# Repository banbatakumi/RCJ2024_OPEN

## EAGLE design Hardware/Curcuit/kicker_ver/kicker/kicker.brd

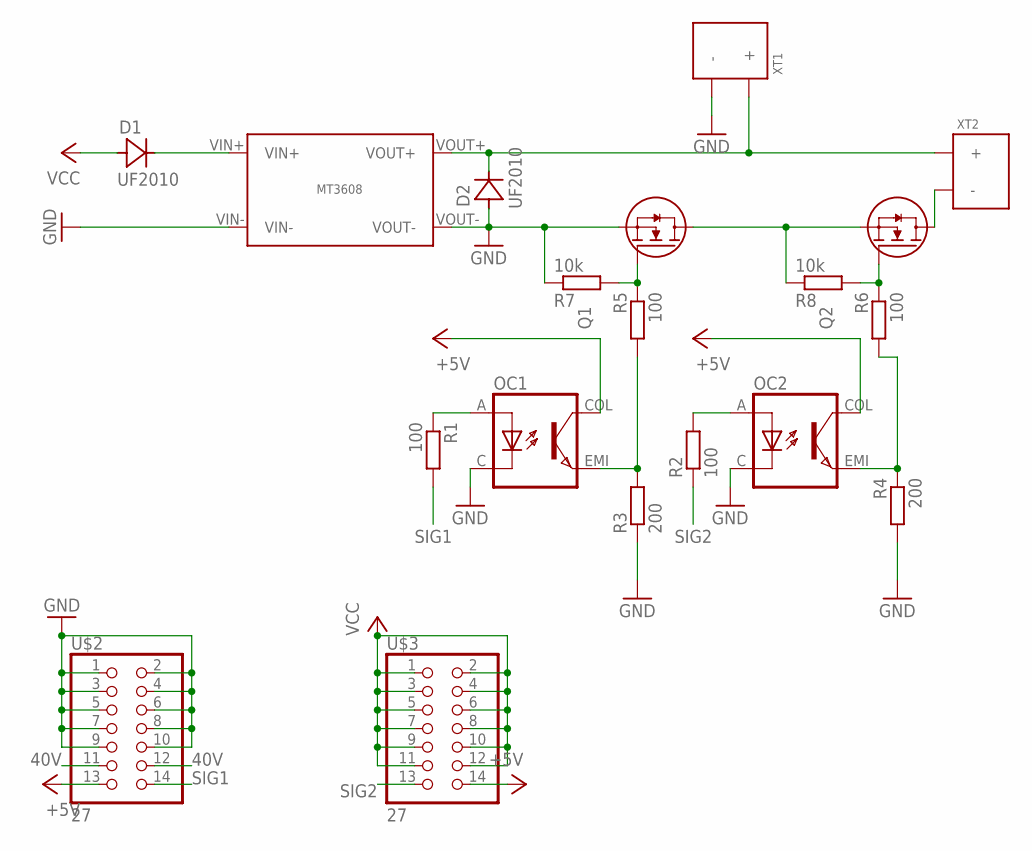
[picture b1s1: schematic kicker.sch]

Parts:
D1, D2: UF2010
OC1, OC2: TL293(GB); SOIC127P700X230-4N
Q1, Q2: NP52N06SLG; TO230P1040X230-3N
R1, R2, R5, R6: 100; R0603
R3, R4: 200; R0603
R7, R8: 10k; R0603
U$1: MT3608
U$2, U$3: 27; 2*7
XT1, XT2: XT30PW-F

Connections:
40V: D2.C, U$1.VOUT+, U$2.11, U$2.12, XT1.+, XT2.+
+5V: OC1.COL, OC2.COL, U$2.13, U$3.14
GND: D2.A, OC1.C, OC2.C, Q1.S, R3.1, R4.2, R7.1, U$1.VIN-, U$1.VOUT-, U$2.1, U$2.2, U$2.3, U$2.4, U$2.5, U$2.6, U$2.7, U$2.8, U$2.9, U$2.10, XT1.-
unnamed: D1.C, U$1.VIN+
unnamed: Q1.D, Q2.S, R8.1
unnamed: OC1.EMI, R3.2, R5.2
unnamed: Q2.D, XT2.-
unnamed: OC1.A, R1.1
unnamed: OC2.A, R2.2
unnamed: OC2.EMI, R4.1, R6.2
unnamed: Q1.G, R5.1, R7.2
unnamed: Q2.G, R6.1, R8.2
SIG1: R1.2, U$2.14
SIG2: R2.1, U$3.13
VCC: D1.A, U$3.1, U$3.2, U$3.3, U$3.4, U$3.5, U$3.6, U$3.7, U$3.8, U$3.9, U$3.10, U$3.11, U$3.12

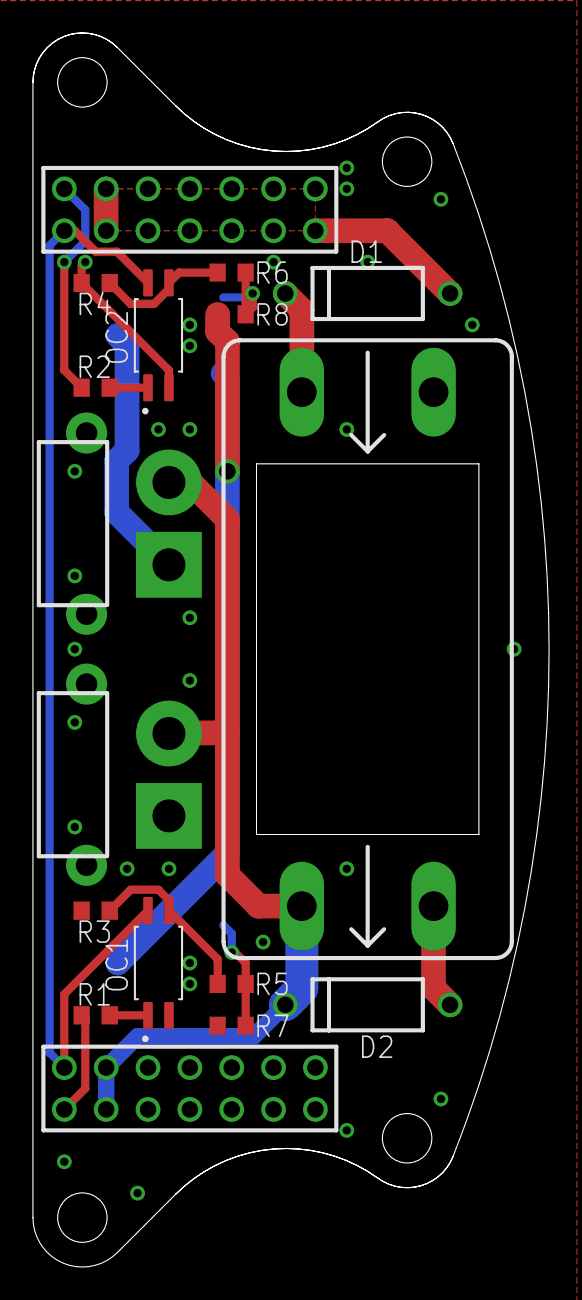
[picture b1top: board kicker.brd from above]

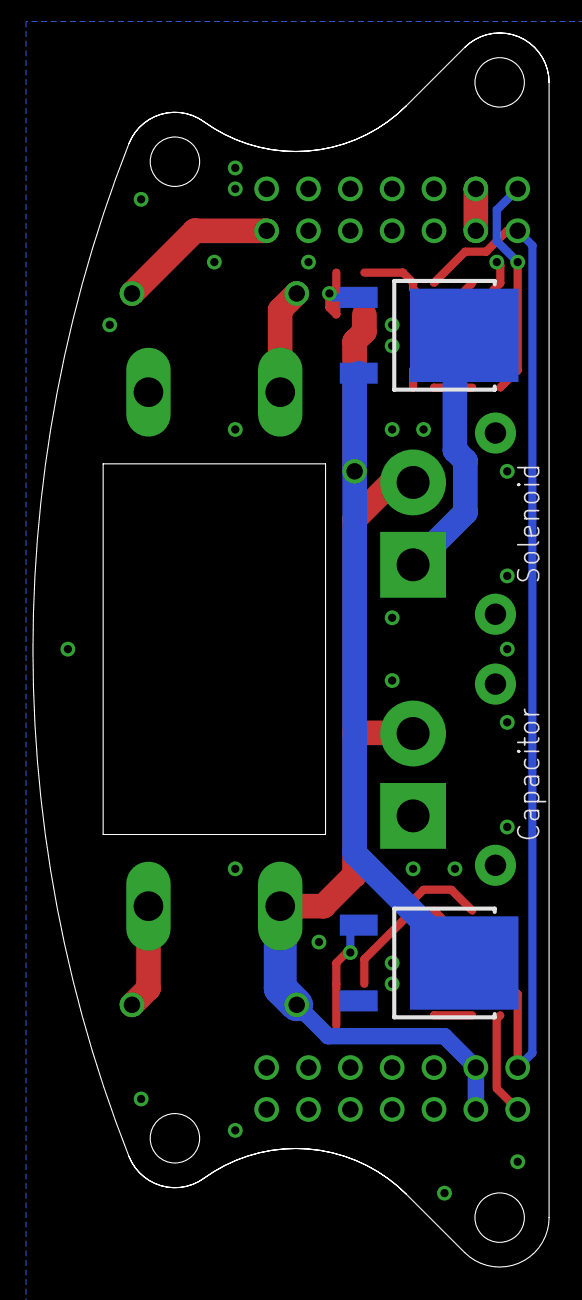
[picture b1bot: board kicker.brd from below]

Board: 2 copper layers, 31.3 x 74.9 mm, 19 parts (2 on the bottom side), 15 nets.

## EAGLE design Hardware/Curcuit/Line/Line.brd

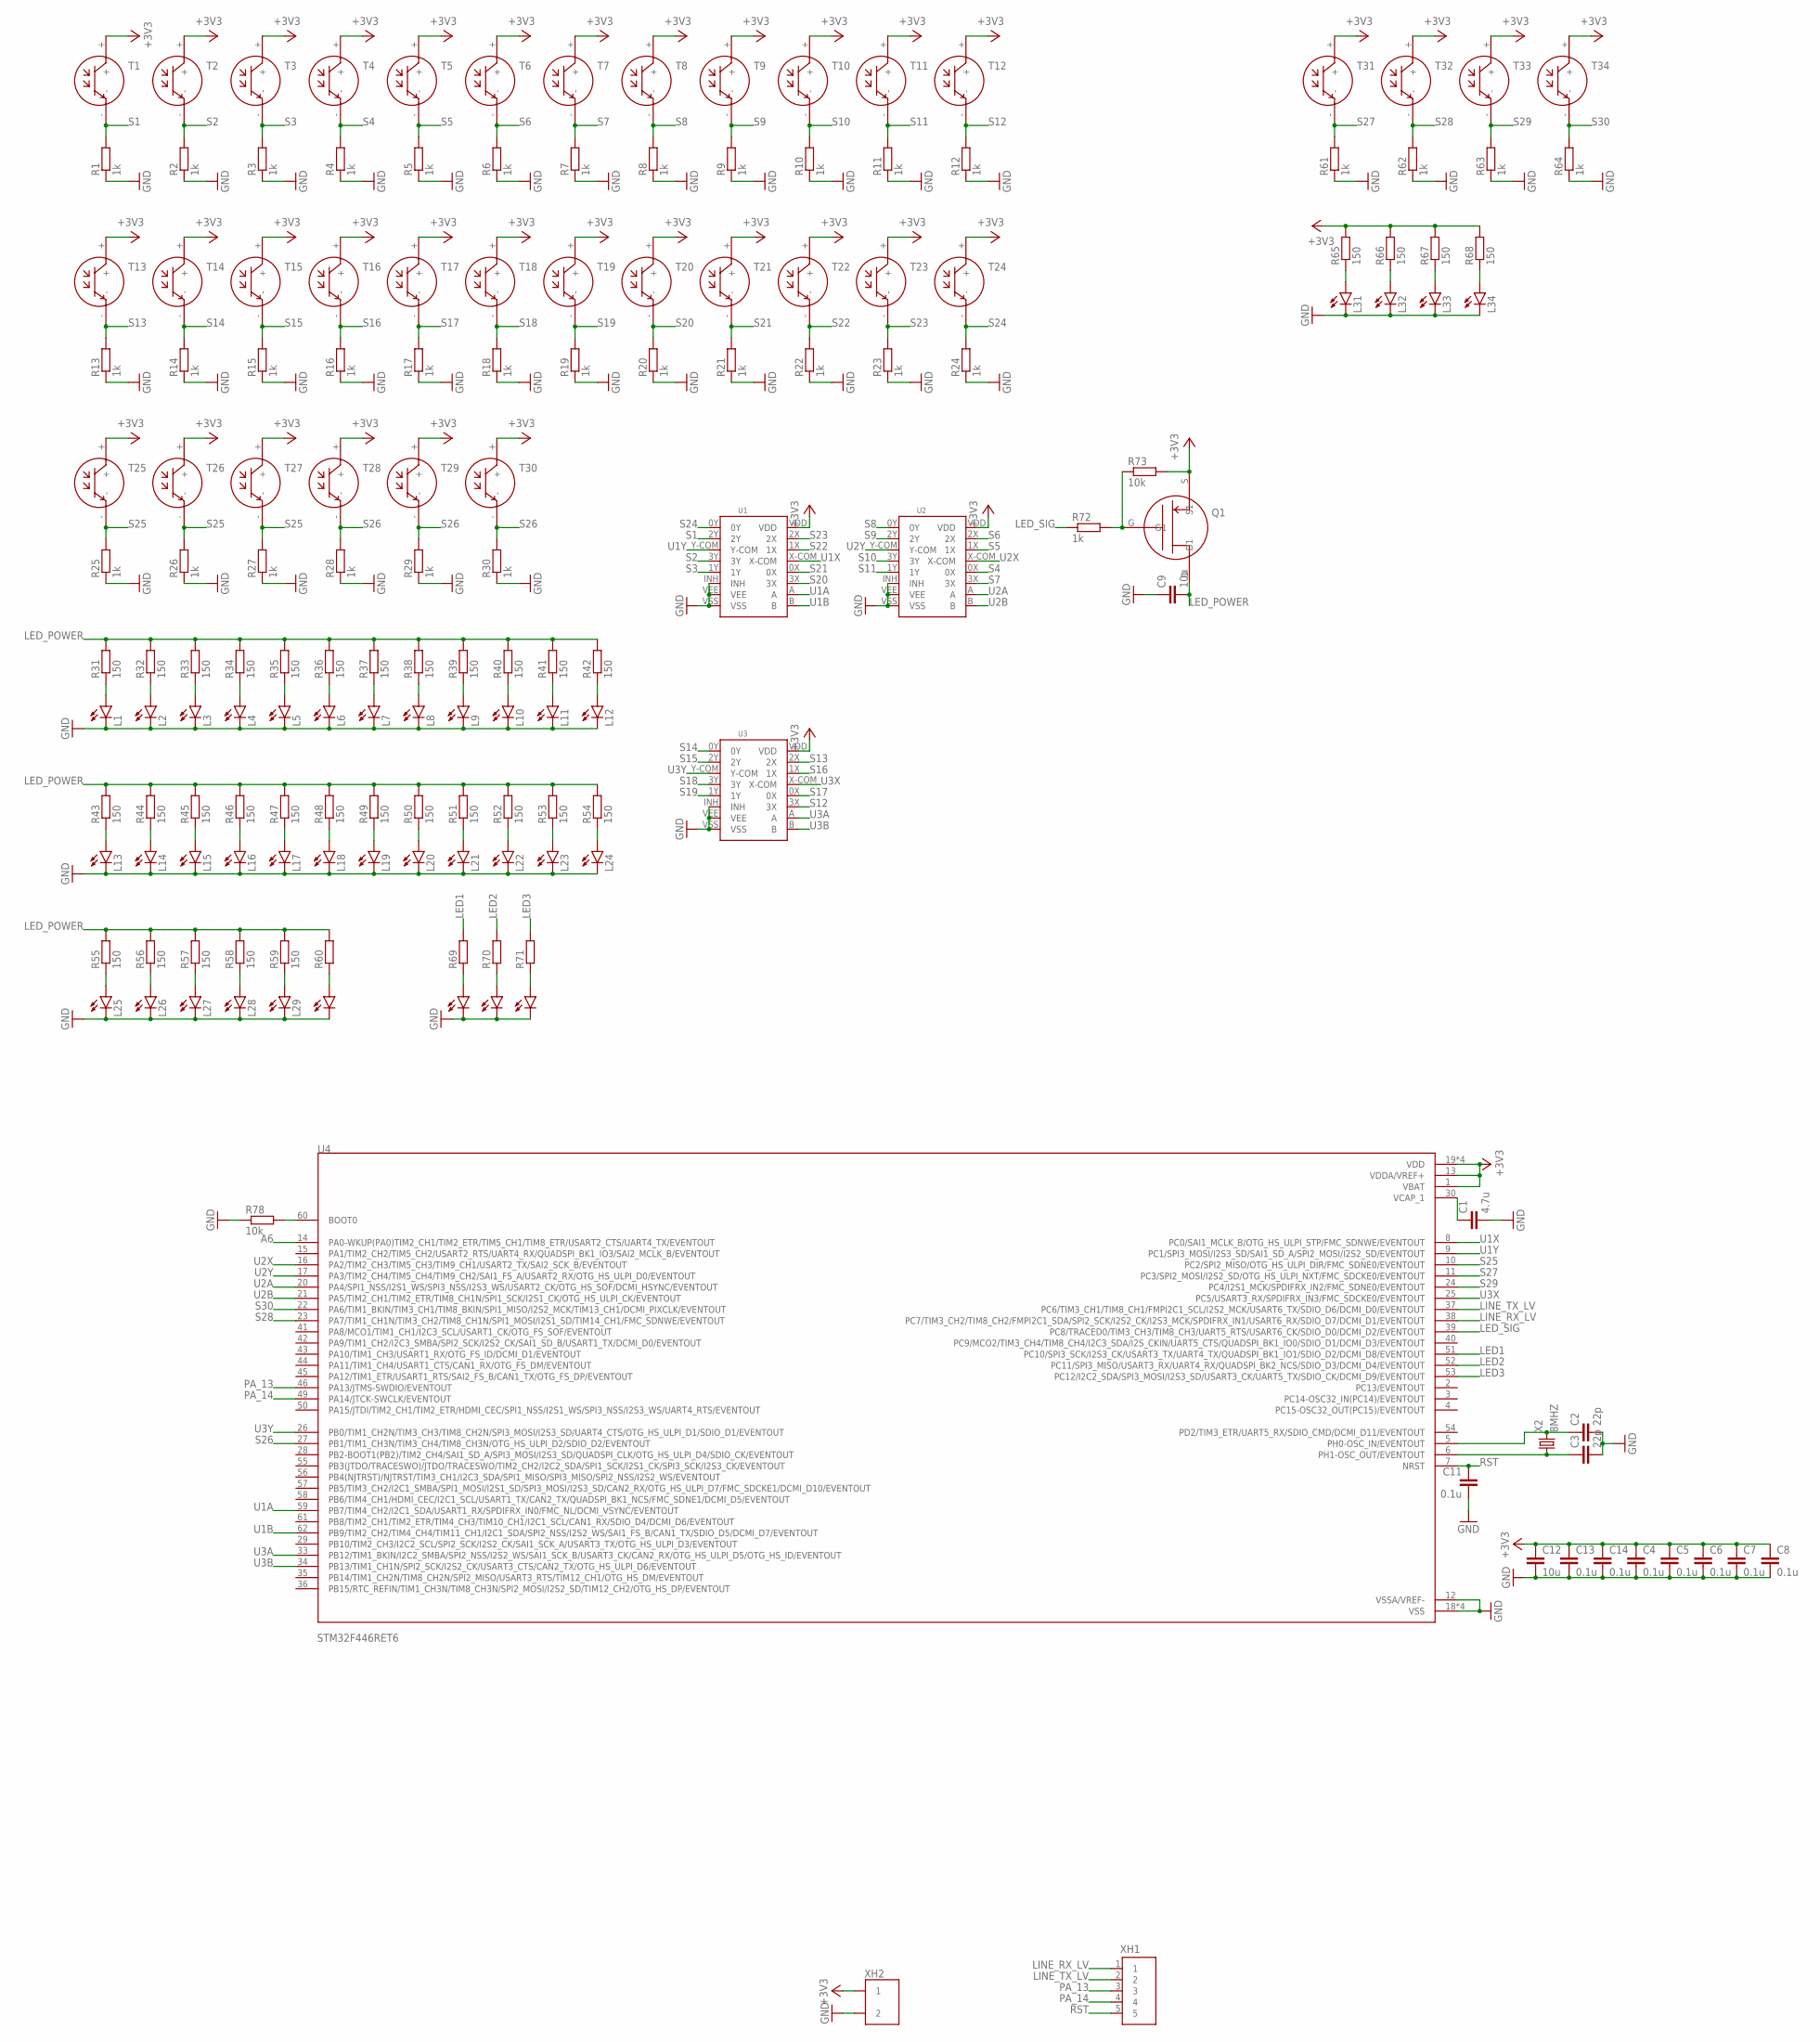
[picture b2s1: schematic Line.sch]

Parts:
C1: 4.7u; C0603
C2, C3: 22p; C0603
C4, C5, C6, C7, C8, C11, C13, C14: 0.1u; C0603
C9, C12: 10u; C0805
L1, L2, L3, L4, L5, L6, L7, L8, L9, L10, L11, L12, L13, L14, L15, L16, L17, L18, L19, L20, L21, L22, L23, L24, L25, L26, L27, L28, L29, L30, L31, L32, L33, L34, L35, L36, L37: SML-E12P8WT86; LED_SML-LXFM0603SIC-TR
Q1: TJ60S04M3L; DPACK
R1, R2, R3, R4, R5, R6, R7, R8, R9, R10, R11, R12, R13, R14, R15, R16, R17, R18, R19, R20, R21, R22, R23, R24, R25, R26, R27, R28, R29, R30, R61, R62, R63, R64, R72: 1k; R0603
R31, R32, R33, R34, R35, R36, R37, R38, R39, R40, R41, R42, R43, R44, R45, R46, R47, R48, R49, R50, R51, R52, R53, R54, R55, R56, R57, R58, R59, R60, R65, R66, R67, R68, R69, R70, R71: 150; R0603
R73, R78: 10k; R0603
T1, T2, T3, T4, T5, T6, T7, T8, T9, T10, T11, T12, T13, T14, T15, T16, T17, T18, T19, T20, T21, T22, T23, T24, T25, T26, T27, T28, T29, T30, T31, T32, T33, T34: NJL7302L-F3
U1, U2, U3: TC4051BP
U4: STM32F446RET6; QFP50P1200X1200X160-64N
X2: 8MHZ; 16MHZ
XH1: 5B
XH2: 2B

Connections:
+3V3: C4.1, C5.1, C6.1, C7.1, C8.1, C12.1, C13.1, C14.1, Q1.S (S1), R65.2, R66.2, R67.2, R68.2, R73.2, T1.+, T2.+, T3.+, T4.+, T5.+, T6.+, T7.+, T8.+, T9.+, T10.+, T11.+, T12.+, T13.+, T14.+, T15.+, T16.+, T17.+, T18.+, T19.+, T20.+, T21.+, T22.+, T23.+, T24.+, T25.+, T26.+, T27.+, T28.+, T29.+, T30.+, T31.+, T32.+, T33.+, T34.+, U1.VDD, U2.VDD, U3.VDD, U4.1 (VBAT), U4.13 (VDDA/VREF+), U4.19 (VDD), U4.32 (VDD), U4.48 (VDD), U4.64 (VDD), XH2.P$1 (1)
A6: U4.14 (PA0-WKUP(PA0)TIM2_CH1/TIM2_ETR/TIM5_CH1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)
GND: C1.2, C2.2, C3.2, C4.2, C5.2, C6.2, C7.2, C8.2, C9.1, C11.2, C12.2, C13.2, C14.2, L1.C, L2.C, L3.C, L4.C, L5.C, L6.C, L7.C, L8.C, L9.C, L10.C, L11.C, L12.C, L13.C, L14.C, L15.C, L16.C, L17.C, L18.C, L19.C, L20.C, L21.C, L22.C, L23.C, L24.C, L25.C, L26.C, L27.C, L28.C, L29.C, L30.C, L31.C, L32.C, L33.C, L34.C, L35.C, L36.C, L37.C, R1.1, R2.1, R3.1, R4.1, R5.1, R6.1, R7.1, R8.1, R9.1, R10.1, R11.1, R12.1, R13.1, R14.1, R15.1, R16.1, R17.1, R18.1, R19.1, R20.1, R21.1, R22.1, R23.1, R24.1, R25.1, R26.1, R27.1, R28.1, R29.1, R30.1, R61.1, R62.1, R63.1, R64.1, R78.1, U1.INH, U1.VEE, U1.VSS, U2.INH, U2.VEE, U2.VSS, U3.INH, U3.VEE, U3.VSS, U4.12 (VSSA/VREF-), U4.18 (VSS), U4.31 (VSS), U4.47 (VSS), U4.63 (VSS), XH2.P$2 (2)
LED1: R69.2, U4.51 (PC10/SPI3_SCK/I2S3_CK/USART3_TX/UART4_T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)
LED2: R70.2, U4.52 (PC11/SPI3_MISO/USART3_RX/UART4_RX/QUADS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)
LED3: R71.2, U4.53 (PC12/I2C2_SDA/SPI3_MOSI/I2S3_SD/USART3_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)
LED_POWER: C9.2, Q1.D (D1), R31.2, R32.2, R33.2, R34.2, R35.2, R36.2, R37.2, R38.2, R39.2, R40.2, R41.2, R42.2, R43.2, R44.2, R45.2, R46.2, R47.2, R48.2, R49.2, R50.2, R51.2, R52.2, R53.2, R54.2, R55.2, R56.2, R57.2, R58.2, R59.2, R60.2
LED_SIG: R72.1, U4.39 (PC8/TRACED0/TIM3_CH3/TIM8_CH3/UART5_RTS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)
LINE_RX_LV: U4.38 (PC7/TIM3_CH2/TIM8_CH2/FMPI2C1_SDA/SPI2_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), XH1.1
LINE_TX_LV: U4.37 (PC6/TIM3_CH1/TIM8_CH1/FMPI2C1_SCL/I2S2_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), XH1.2
unnamed: L1.A, R31.1
unnamed: L2.A, R32.1
unnamed: L3.A, R33.1
unnamed: L4.A, R34.1
unnamed: L5.A, R35.1
unnamed: L6.A, R36.1
unnamed: L7.A, R37.1
unnamed: L8.A, R38.1
unnamed: L9.A, R39.1
unnamed: L10.A, R40.1
unnamed: L11.A, R41.1
unnamed: L12.A, R42.1
unnamed: L13.A, R43.1
unnamed: L14.A, R44.1
unnamed: L15.A, R45.1
unnamed: L16.A, R46.1
unnamed: L17.A, R47.1
unnamed: L18.A, R48.1
unnamed: L19.A, R49.1
unnamed: L20.A, R50.1
unnamed: L21.A, R51.1
unnamed: L22.A, R52.1
unnamed: L23.A, R53.1
unnamed: L24.A, R54.1
unnamed: L25.A, R55.1
unnamed: L26.A, R56.1
unnamed: L27.A, R57.1
unnamed: L28.A, R58.1
unnamed: L29.A, R59.1
unnamed: L30.A, R60.1
unnamed: L31.A, R65.1
unnamed: L32.A, R66.1
unnamed: L33.A, R67.1
unnamed: L34.A, R68.1
unnamed: L35.A, R69.1
unnamed: L36.A, R70.1
unnamed: L37.A, R71.1
unnamed: Q1.G (G1), R72.2, R73.1
unnamed: C1.1, U4.30 (VCAP_1)
unnamed: R78.2, U4.60 (BOOT0)
unnamed: C2.1, U4.5 (PH0-OSC_IN/EVENTOUT), X2.P$2 (2)
unnamed: C3.1, U4.6 (PH1-OSC_OUT/EVENTOUT), X2.P$1 (1)
PA_13: U4.46 (PA13/JTMS-SWDIO/EVENTOUT), XH1.3
PA_14: U4.49 (PA14/JTCK-SWCLK/EVENTOUT), XH1.4
RST: C11.1, U4.7 (NRST), XH1.5
S1: R1.2, T1.-, U1.2Y
S2: R2.2, T2.-, U1.3Y
S3: R3.2, T3.-, U1.1Y
S4: R4.2, T4.-, U2.0X
S5: R5.2, T5.-, U2.1X
S6: R6.2, T6.-, U2.2X
S7: R7.2, T7.-, U2.3X
S8: R8.2, T8.-, U2.0Y
S9: R9.2, T9.-, U2.2Y
S10: R10.2, T10.-, U2.3Y
S11: R11.2, T11.-, U2.1Y
S12: R12.2, T12.-, U3.3X
S13: R13.2, T13.-, U3.2X
S14: R14.2, T14.-, U3.0Y
S15: R15.2, T15.-, U3.2Y
S16: R16.2, T16.-, U3.1X
S17: R17.2, T17.-, U3.0X
S18: R18.2, T18.-, U3.3Y
S19: R19.2, T19.-, U3.1Y
S20: R20.2, T20.-, U1.3X
S21: R21.2, T21.-, U1.0X
S22: R22.2, T22.-, U1.1X
S23: R23.2, T23.-, U1.2X
S24: R24.2, T24.-, U1.0Y
S25: R25.2, R26.2, R27.2, T25.-, T26.-, T27.-, U4.10 (PC2/SPI2_MISO/OTG_HS_ULPI_DIR/FMC_SDNE0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)
S26: R28.2, R29.2, R30.2, T28.-, T29.-, T30.-, U4.27 (PB1/TIM1_CH3N/TIM3_CH4/TIM8_CH3N/OTG_HS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)
S27: R61.2, T31.-, U4.11 (PC3/SPI2_MOSI/I2S2_SD/OTG_HS_ULPI_NXT/F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)
S28: R62.2, T32.-, U4.23 (PA7/TIM1_CH1N/TIM3_CH2/TIM8_CH1N/SPI1_M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)
S29: R63.2, T33.-, U4.24 (PC4/I2S1_MCK/SPDIFRX_IN2/FMC_SDNE0/EVEN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)
S30: R64.2, T34.-, U4.22 (PA6/TIM1_BKIN/TIM3_CH1/TIM8_BKIN/SPI1_M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)
U1A: U1.A, U4.59 (PB7/TIM4_CH2/I2C1_SDA/USART1_RX/SPDIFRX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)
U1B: U1.B, U4.62 (PB9/TIM2_CH2/TIM4_CH4/TIM11_CH1/I2C1_SD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)
U1X: U1.X-COM, U4.8 (PC0/SAI1_MCLK_B/OTG_HS_ULPI_STP/FMC_SDN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)
U1Y: U1.Y-COM, U4.9 (PC1/SPI3_MOSI/I2S3_SD/SAI1_SD_A/SPI2_MO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)
U2A: U2.A, U4.20 (PA4/SPI1_NSS/I2S1_WS/SPI3_NSS/I2S3_WS/U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)
U2B: U2.B, U4.21 (PA5/TIM2_CH1/TIM2_ETR/TIM8_CH1N/SPI1_SC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)
U2X: U2.X-COM, U4.16 (PA2/TIM2_CH3/TIM5_CH3/TIM9_CH1/USART2_T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)
U2Y: U2.Y-COM, U4.17 (PA3/TIM2_CH4/TIM5_CH4/TIM9_CH2/SAI1_FS_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)
U3A: U3.A, U4.33 (PB12/TIM1_BKIN/I2C2_SMBA/SPI2_NSS/I2S2_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)
U3B: U3.B, U4.34 (PB13/TIM1_CH1N/SPI2_SCK/I2S2_CK/USART3_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)
U3X: U3.X-COM, U4.25 (PC5/USART3_RX/SPDIFRX_IN3/FMC_SDCKE0/EV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)
U3Y: U3.Y-COM, U4.26 (PB0/TIM1_CH2N/TIM3_CH3/TIM8_CH2N/SPI3_M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)

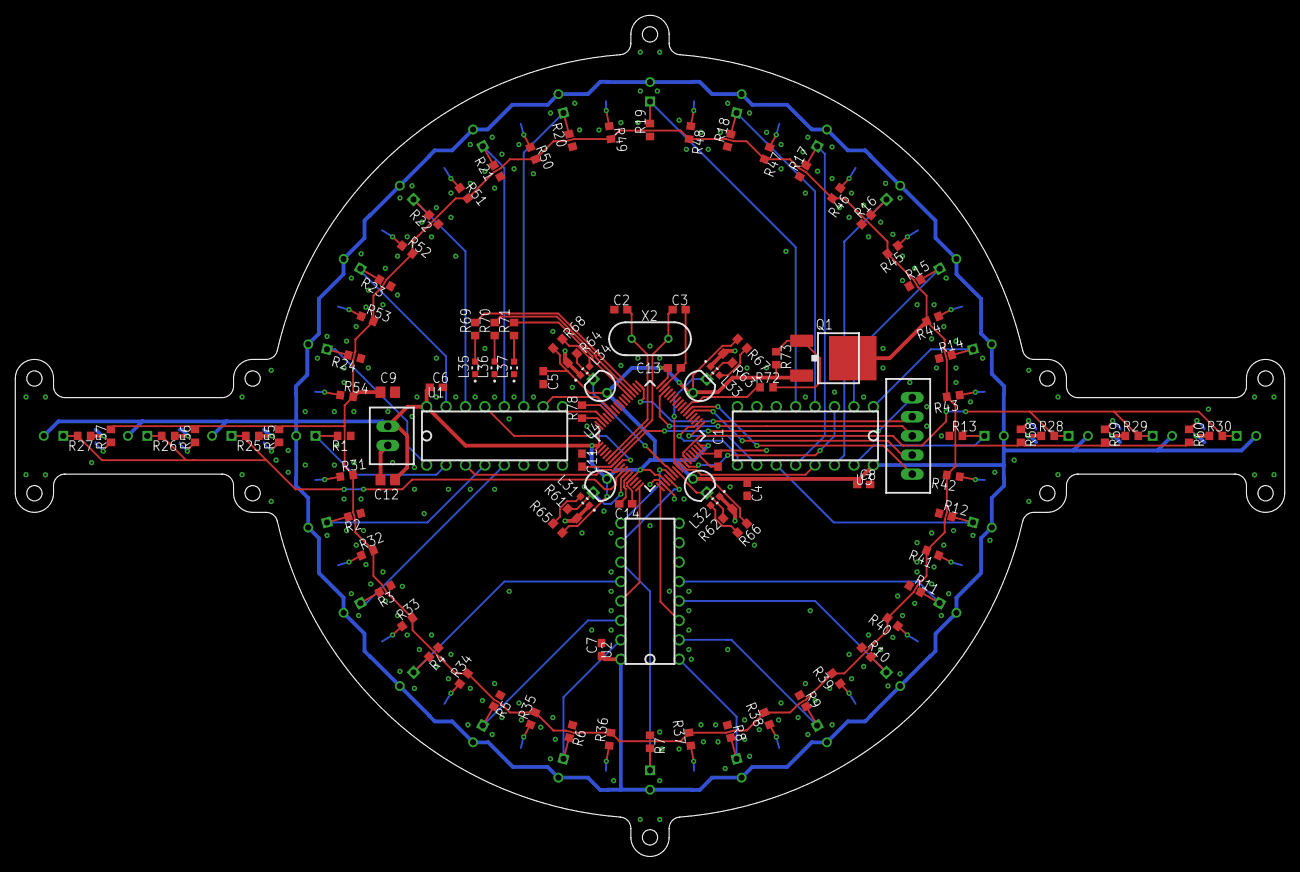
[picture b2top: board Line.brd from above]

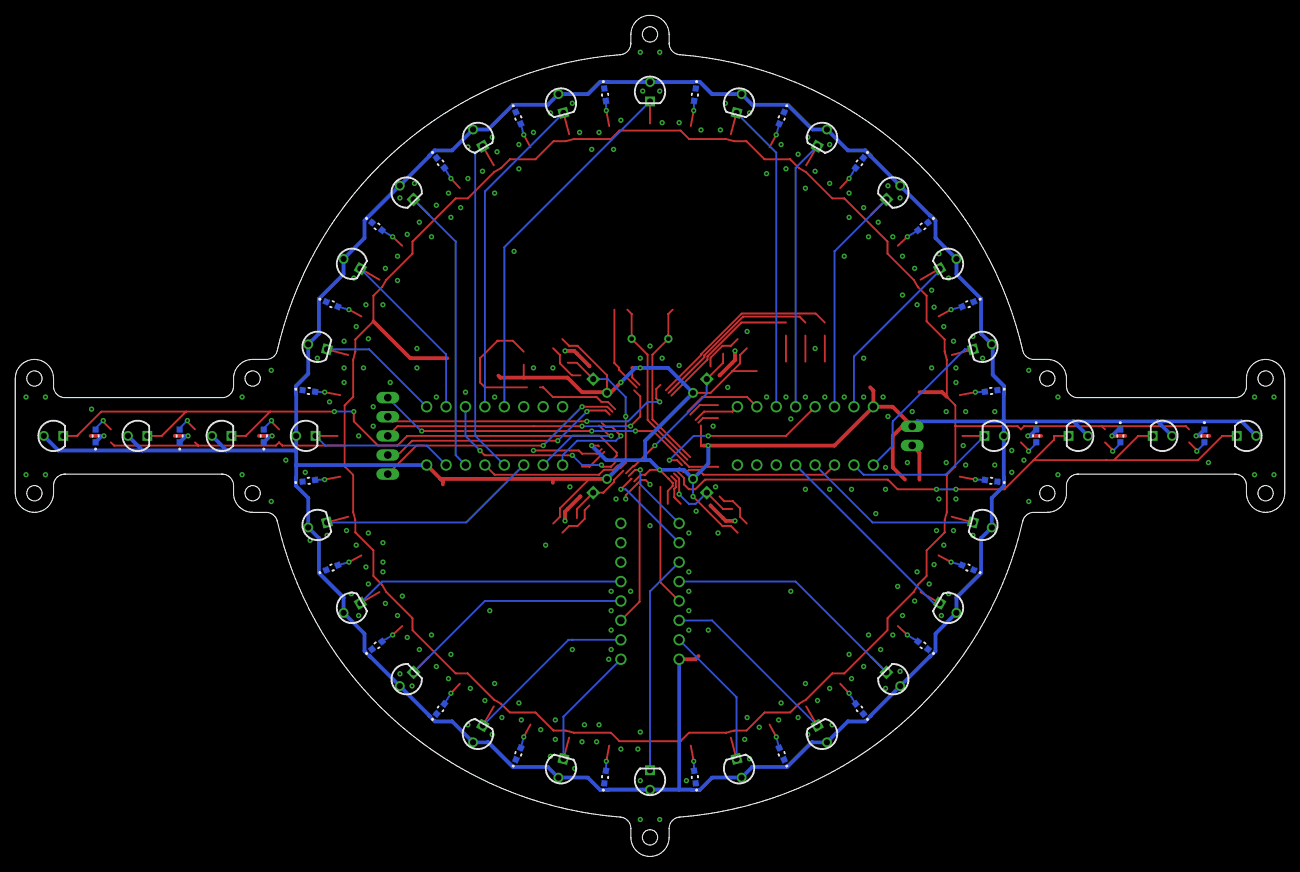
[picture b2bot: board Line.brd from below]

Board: 2 copper layers, 166.0 x 110.0 mm, 166 parts (60 on the bottom side), 96 nets.

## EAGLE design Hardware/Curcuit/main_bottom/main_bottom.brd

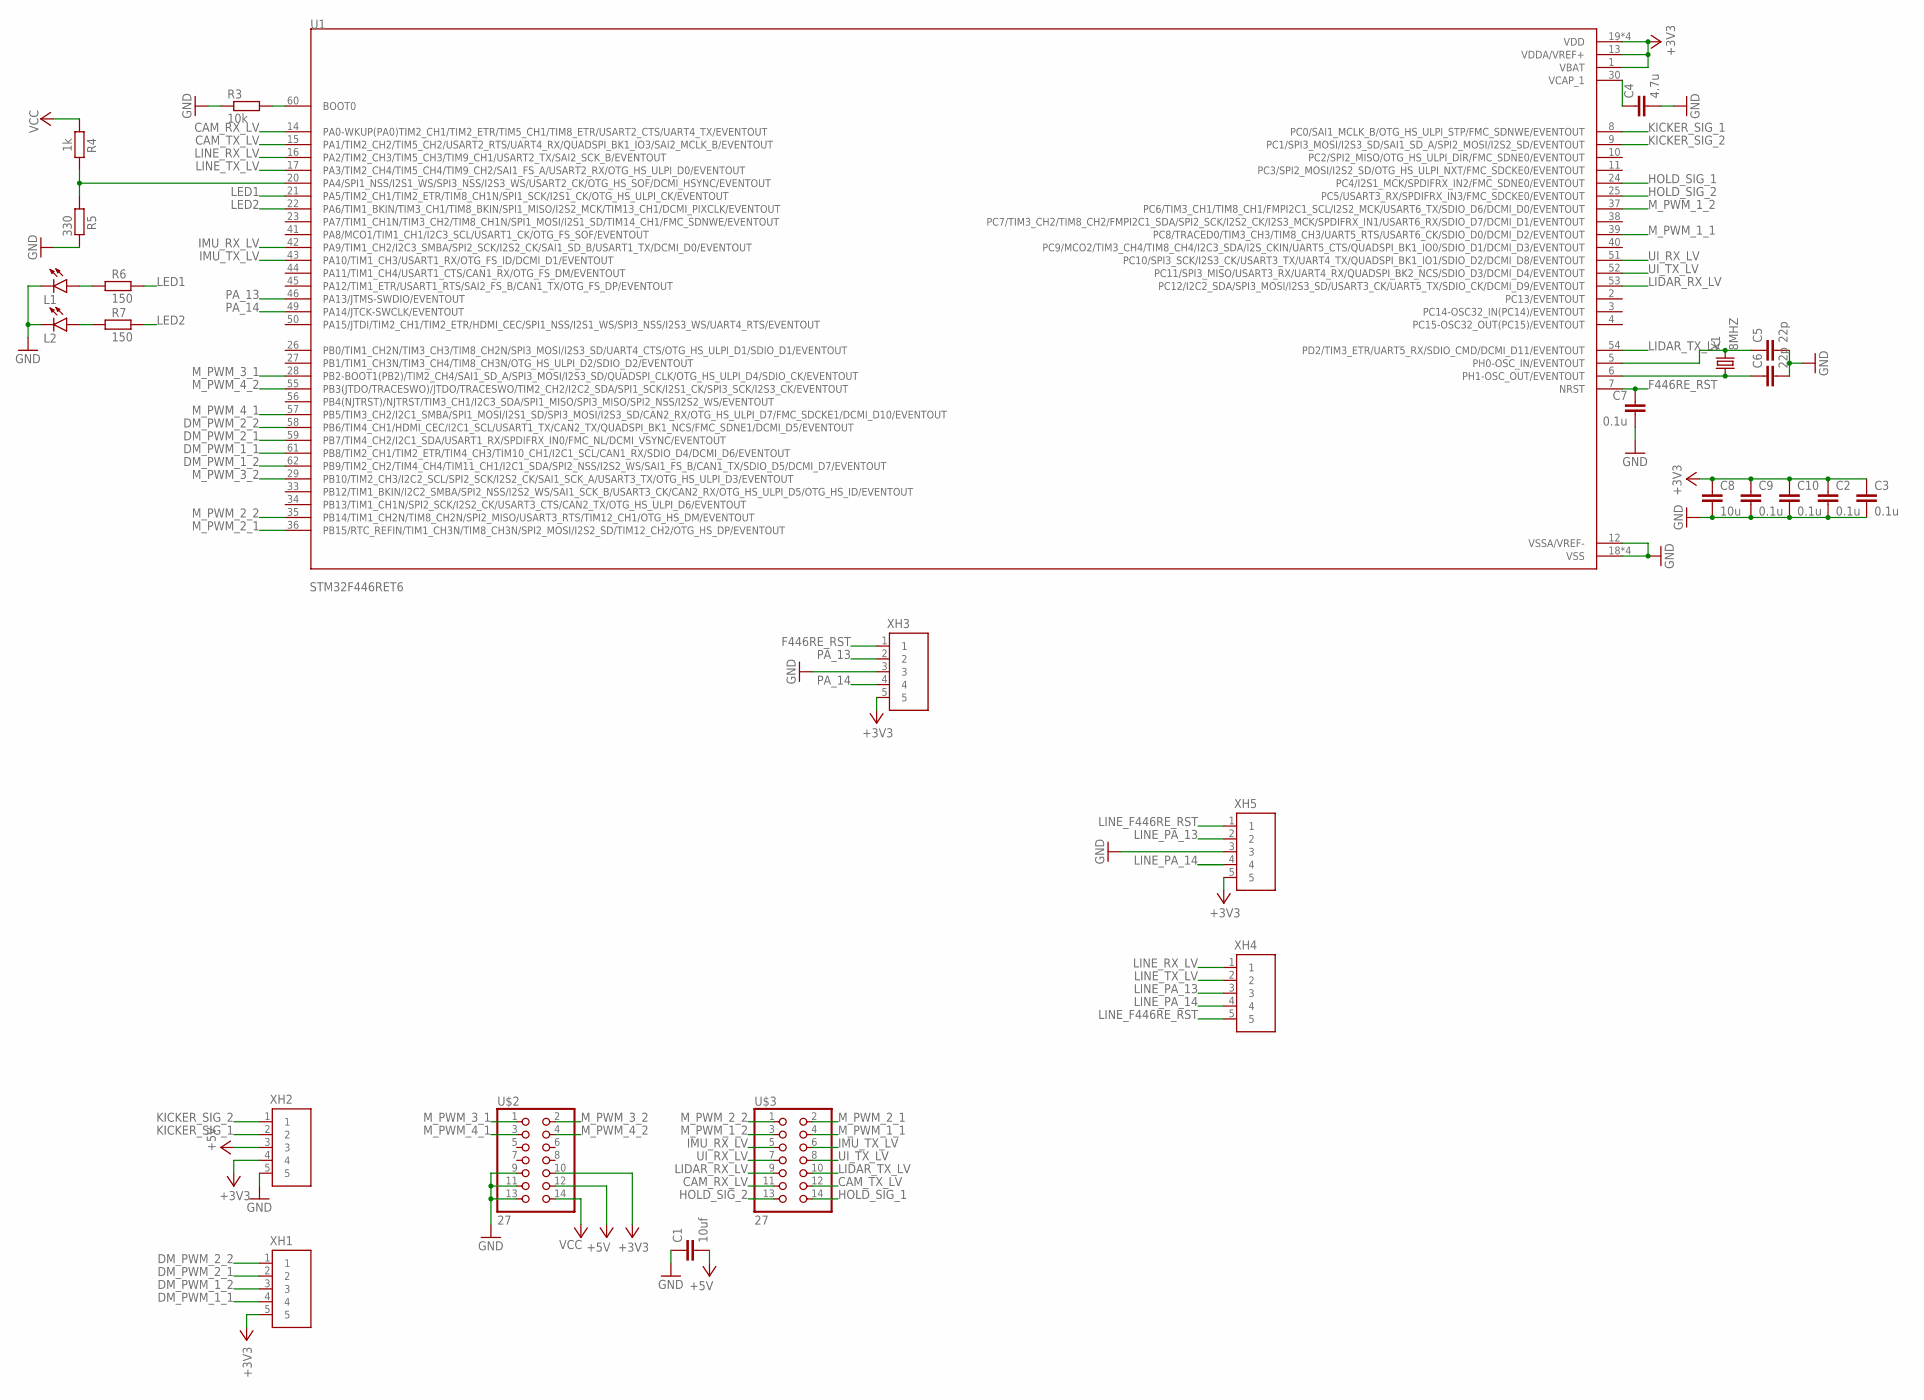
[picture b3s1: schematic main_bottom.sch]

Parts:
C1: 10uf; C0805
C2, C3, C7, C9, C10: 0.1u; C0603
C4: 4.7u; C0603
C5, C6: 22p; C0603
C8: 10u; C0805
L1, L2: SML-E12P8WT86; LED_SML-LXFM0603SIC-TR
R3: 10k; R0603
R4: 1k; R0603
R5: 330; R0603
R6, R7: 150; R0603
U1: STM32F446RET6; QFP50P1200X1200X160-64N
U$2, U$3: 27; 2*7
X1: 8MHZ; 16MHZ
XH1, XH2, XH3, XH4, XH5: S5B

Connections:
+3V3: C2.1, C3.1, C8.1, C9.1, C10.1, U1.1 (VBAT), U1.13 (VDDA/VREF+), U1.19 (VDD), U1.32 (VDD), U1.48 (VDD), U1.64 (VDD), U$2.10, XH1.5, XH2.4, XH3.5, XH5.5
+5V: C1.2, U$2.12, XH2.3
CAM_RX_LV: U1.14 (PA0-WKUP(PA0)TIM2_CH1/TIM2_ETR/TIM5_CH1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), U$3.11
CAM_TX_LV: U1.15 (PA1/TIM2_CH2/TIM5_CH2/USART2_RTS/UART4_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), U$3.12
DM_PWM_1_1: U1.61 (PB8/TIM2_CH1/TIM2_ETR/TIM4_CH3/TIM10_CH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), XH1.4
DM_PWM_1_2: U1.62 (PB9/TIM2_CH2/TIM4_CH4/TIM11_CH1/I2C1_SD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), XH1.3
DM_PWM_2_1: U1.59 (PB7/TIM4_CH2/I2C1_SDA/USART1_RX/SPDIFRX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), XH1.2
DM_PWM_2_2: U1.58 (PB6/TIM4_CH1/HDMI_CEC/I2C1_SCL/USART1_T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), XH1.1
F446RE_RST: C7.1, U1.7 (NRST), XH3.1
GND: C1.1, C2.2, C3.2, C4.2, C5.2, C6.2, C7.2, C8.2, C9.2, C10.2, L1.C, L2.C, R3.1, R5.2, U1.12 (VSSA/VREF-), U1.18 (VSS), U1.31 (VSS), U1.47 (VSS), U1.63 (VSS), U$2.9, U$2.11, U$2.13, XH2.5, XH3.3, XH5.3
HOLD_SIG_1: U1.24 (PC4/I2S1_MCK/SPDIFRX_IN2/FMC_SDNE0/EVEN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), U$3.14
HOLD_SIG_2: U1.25 (PC5/USART3_RX/SPDIFRX_IN3/FMC_SDCKE0/EV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), U$3.13
IMU_RX_LV: U1.42 (PA9/TIM1_CH2/I2C3_SMBA/SPI2_SCK/I2S2_CK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), U$3.5
IMU_TX_LV: U1.43 (PA10/TIM1_CH3/USART1_RX/OTG_FS_ID/DCMI_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), U$3.6
KICKER_SIG_1: U1.8 (PC0/SAI1_MCLK_B/OTG_HS_ULPI_STP/FMC_SDN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), XH2.2
KICKER_SIG_2: U1.9 (PC1/SPI3_MOSI/I2S3_SD/SAI1_SD_A/SPI2_MO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), XH2.1
LED1: R6.2, U1.21 (PA5/TIM2_CH1/TIM2_ETR/TIM8_CH1N/SPI1_SC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)
LED2: R7.2, U1.22 (PA6/TIM1_BKIN/TIM3_CH1/TIM8_BKIN/SPI1_M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)
LIDAR_RX_LV: U1.53 (PC12/I2C2_SDA/SPI3_MOSI/I2S3_SD/USART3_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), U$3.9
LIDAR_TX_LV: U1.54 (PD2/TIM3_ETR/UART5_RX/SDIO_CMD/DCMI_D11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), U$3.10
LINE_F446RE_RST: XH4.5, XH5.1
LINE_PA_13: XH4.3, XH5.2
LINE_PA_14: XH4.4, XH5.4
LINE_RX_LV: U1.16 (PA2/TIM2_CH3/TIM5_CH3/TIM9_CH1/USART2_T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), XH4.1
LINE_TX_LV: U1.17 (PA3/TIM2_CH4/TIM5_CH4/TIM9_CH2/SAI1_FS_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), XH4.2
M_PWM_1_1: U1.39 (PC8/TRACED0/TIM3_CH3/TIM8_CH3/UART5_RTS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), U$3.4
M_PWM_1_2: U1.37 (PC6/TIM3_CH1/TIM8_CH1/FMPI2C1_SCL/I2S2_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), U$3.3
M_PWM_2_1: U1.36 (PB15/RTC_REFIN/TIM1_CH3N/TIM8_CH3N/SPI2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), U$3.2
M_PWM_2_2: U1.35 (PB14/TIM1_CH2N/TIM8_CH2N/SPI2_MISO/USAR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), U$3.1
M_PWM_3_1: U1.28 (PB2-BOOT1(PB2)/TIM2_CH4/SAI1_SD_A/SPI3_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), U$2.1
M_PWM_3_2: U1.29 (PB10/TIM2_CH3/I2C2_SCL/SPI2_SCK/I2S2_CK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), U$2.2
M_PWM_4_1: U1.57 (PB5/TIM3_CH2/I2C1_SMBA/SPI1_MOSI/I2S1_S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), U$2.3
M_PWM_4_2: U1.55 (PB3(JTDO/TRACESWO)/JTDO/TRACESWO/TIM2_C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), U$2.4
unnamed: C4.1, U1.30 (VCAP_1)
unnamed: R3.2, U1.60 (BOOT0)
unnamed: C5.1, U1.5 (PH0-OSC_IN/EVENTOUT), X1.P$2 (2)
unnamed: C6.1, U1.6 (PH1-OSC_OUT/EVENTOUT), X1.P$1 (1)
unnamed: L2.A, R7.1
unnamed: L1.A, R6.1
PA_13: U1.46 (PA13/JTMS-SWDIO/EVENTOUT), XH3.2
PA_14: U1.49 (PA14/JTCK-SWCLK/EVENTOUT), XH3.4
UI_RX_LV: U1.51 (PC10/SPI3_SCK/I2S3_CK/USART3_TX/UART4_T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), U$3.7
UI_TX_LV: U1.52 (PC11/SPI3_MISO/USART3_RX/UART4_RX/QUADS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), U$3.8
VCC: R4.1, U$2.14
VCC_SIG: R4.2, R5.1, U1.20 (PA4/SPI1_NSS/I2S1_WS/SPI3_NSS/I2S3_WS/U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)

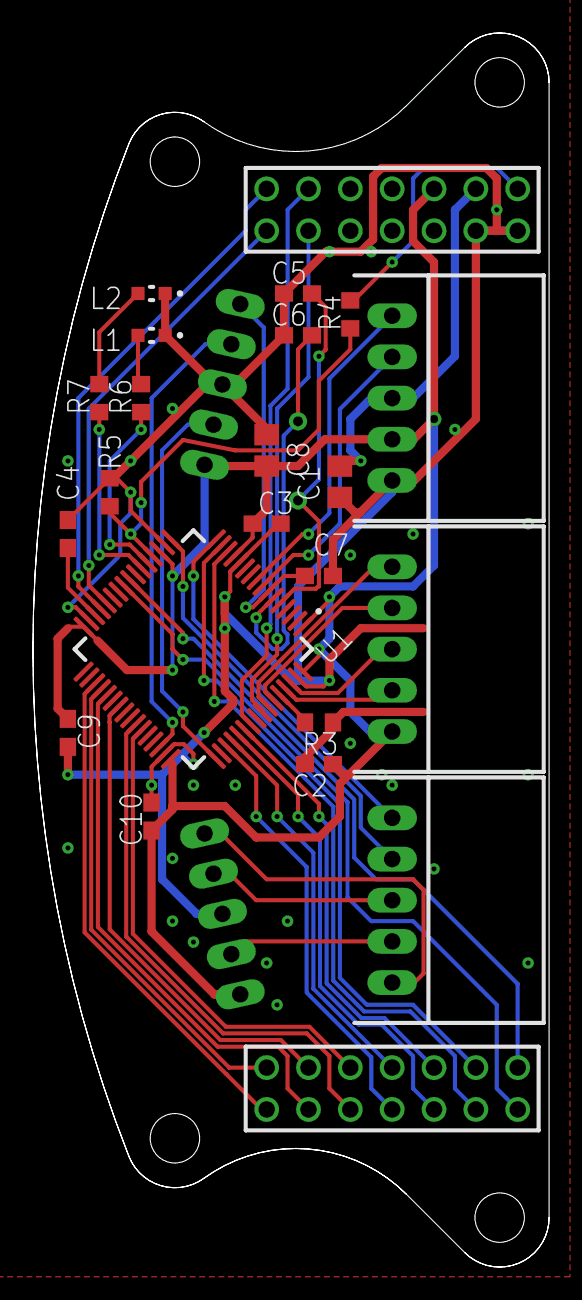
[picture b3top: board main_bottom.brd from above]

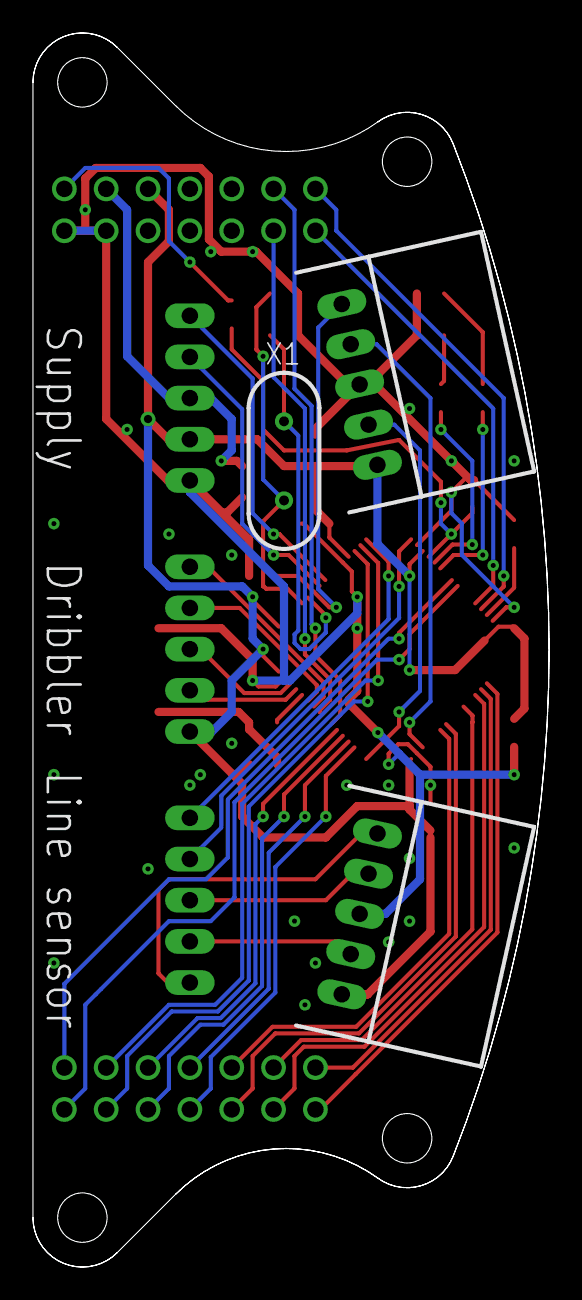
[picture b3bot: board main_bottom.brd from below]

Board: 2 copper layers, 31.3 x 74.9 mm, 26 parts (3 on the bottom side), 45 nets.

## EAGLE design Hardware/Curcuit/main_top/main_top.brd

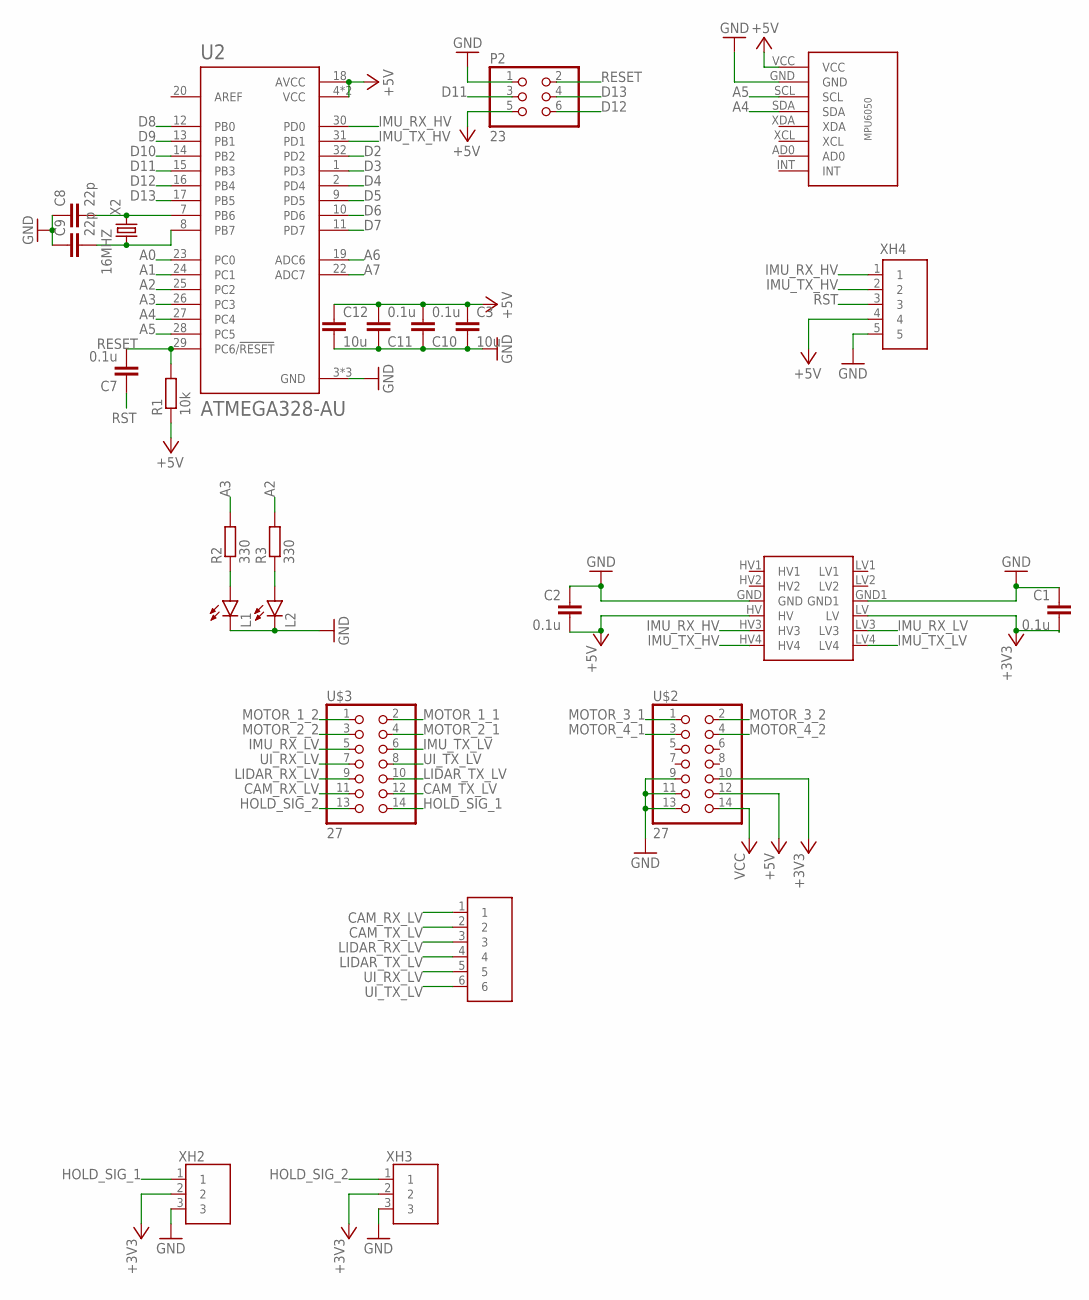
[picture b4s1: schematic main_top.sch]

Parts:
C1, C2, C7, C10, C11: 0.1u; C0603
C3, C12: 10u; C0805
C8, C9: 22p; C0603
L1, L2: SML-E12P8WT86; LED_SML-LXFM0603SIC-TR
P2: 23; 2*3
Q1: BSS138
R1: 10k; 0204/5
R2, R3: 330; 0204/5
U2: ATMEGA328-AU; QFP80P900X900X120-32N
U$1: MPU6050
U$2, U$3: 27; 2*7
X2: 16MHZ
XH1: S6B
XH2, XH3: S3B
XH4: S5B

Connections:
+3V3: C1.2, Q1.LV, U$2.10, XH2.2, XH3.2
+5V: C2.2, C3.1, C10.2, C11.2, C12.1, P2.5, Q1.HV, R1.1, U2.4 (VCC), U2.6 (VCC), U2.18 (AVCC), U$1.VCC, U$2.12, XH4.4
A0: U2.23 (PC0)
A1: U2.24 (PC1)
A2: R3.2, U2.25 (PC2)
A3: R2.2, U2.26 (PC3)
A4: U2.27 (PC4), U$1.SDA
A5: U2.28 (PC5), U$1.SCL
A6: U2.19 (ADC6)
A7: U2.22 (ADC7)
CAM_RX_LV: U$3.11, XH1.1
CAM_TX_LV: U$3.12, XH1.2
D2: U2.32 (PD2)
D3: U2.1 (PD3)
D4: U2.2 (PD4)
D5: U2.9 (PD5)
D6: U2.10 (PD6)
D7: U2.11 (PD7)
D8: U2.12 (PB0)
D9: U2.13 (PB1)
D10: U2.14 (PB2)
D11: P2.3, U2.15 (PB3)
D12: P2.6, U2.16 (PB4)
D13: P2.4, U2.17 (PB5)
GND: C1.1, C2.1, C3.2, C8.1, C9.1, C10.1, C11.1, C12.2, L1.C, L2.C, P2.1, Q1.GND, Q1.GND1, U2.3 (GND), U2.5 (GND), U2.21 (GND), U$1.GND, U$2.9, U$2.11, U$2.13, XH2.3, XH3.3, XH4.5
HOLD_SIG_1: U$3.14, XH2.1
HOLD_SIG_2: U$3.13, XH3.1
IMU_RX_HV: Q1.HV3, U2.30 (PD0), XH4.1
IMU_RX_LV: Q1.LV3, U$3.5
IMU_TX_HV: Q1.HV4, U2.31 (PD1), XH4.2
IMU_TX_LV: Q1.LV4, U$3.6
LIDAR_RX_LV: U$3.9, XH1.3
LIDAR_TX_LV: U$3.10, XH1.4
MOTOR_1_1: U$3.2
MOTOR_1_2: U$3.1
MOTOR_2_1: U$3.4
MOTOR_2_2: U$3.3
MOTOR_3_1: U$2.1
MOTOR_3_2: U$2.2
MOTOR_4_1: U$2.3
MOTOR_4_2: U$2.4
unnamed: C8.2, U2.7 (PB6), X2.P$2 (2)
unnamed: C9.2, U2.8 (PB7), X2.P$1 (1)
unnamed: L1.A, R2.1
unnamed: L2.A, R3.1
RESET: C7.2, P2.2, R1.2, U2.29 (PC6/!RESET)
RST: C7.1, XH4.3
UI_RX_LV: U$3.7, XH1.5
UI_TX_LV: U$3.8, XH1.6
VCC: U$2.14
